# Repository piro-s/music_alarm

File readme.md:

# Music alarm:  
Playing music (sound signals) when the signal line breaks.  

### Schemes:  
###### Music_alarm_v0.1:  
[pdf](docs/music_alarm_v0.1.pdf)  

### Images:  
###### Music_alarm_v0.1:  
top:  
  
bottom:  

###### gerber:  
Archive for production:  
[Music_alarm_v0.1](https://github.com/piro-s/music_alarm/raw/main/gerber/music_alarm_v0.1.zip)

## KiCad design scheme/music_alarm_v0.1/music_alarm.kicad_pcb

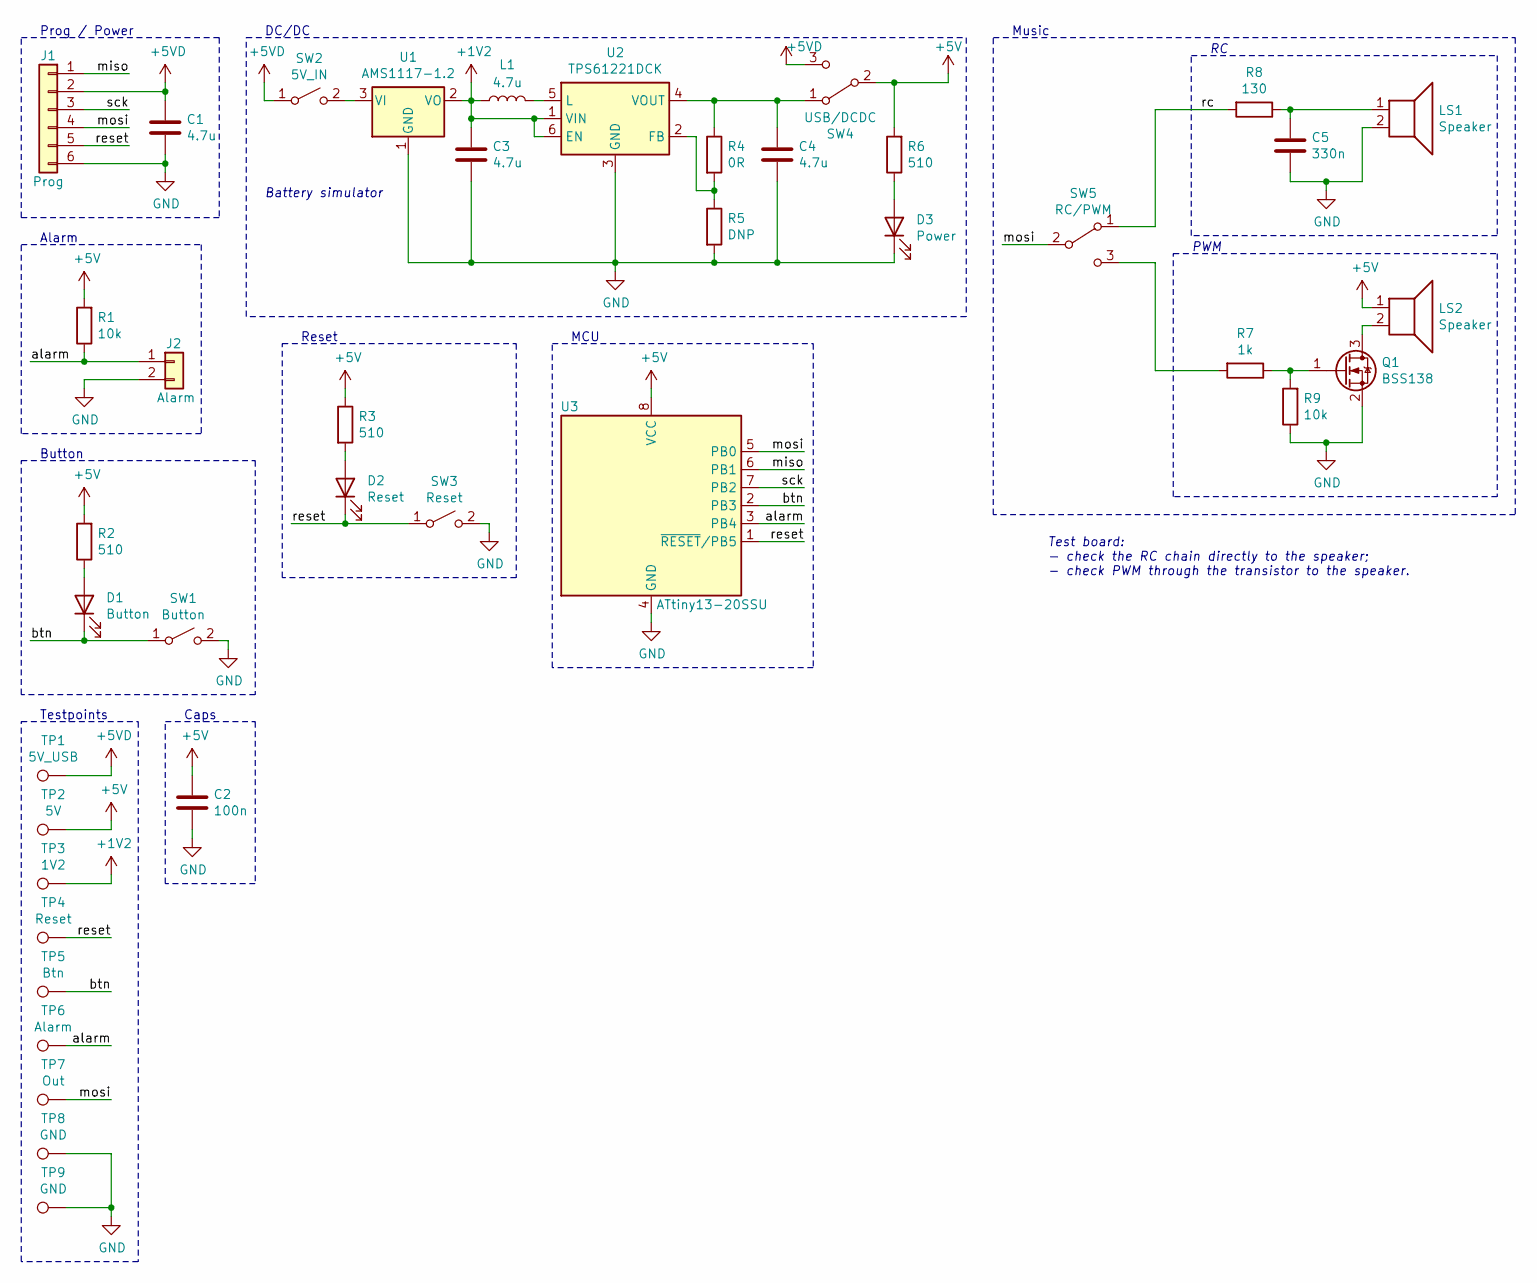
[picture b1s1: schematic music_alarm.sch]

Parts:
C1, C3, C4: 4.7u; C_1206_3216Metric_Pad1.33x1.80mm_HandSolder
C2: 100n; C_0603_1608Metric_Pad1.08x0.95mm_HandSolder
C5: 330n; C_0603_1608Metric_Pad1.08x0.95mm_HandSolder
D1: Button; LED_0603_1608Metric_Pad1.05x0.95mm_HandSolder
D2: Reset; LED_0603_1608Metric_Pad1.05x0.95mm_HandSolder
D3: Power; LED_0603_1608Metric_Pad1.05x0.95mm_HandSolder
J1: Prog; IDC-Header_2x06_P2.54mm_Vertical
J2: Alarm; PinSocket_1x02_P1.27mm_Vertical
L1: 4.7u; L_0805_2012Metric_Pad1.05x1.20mm_HandSolder
LS1, LS2: Speaker; PinSocket_1x02_P1.27mm_Vertical
Q1: BSS138; SOT-23
R1, R9: 10k; R_0603_1608Metric_Pad0.98x0.95mm_HandSolder
R2, R3, R6: 510; R_0603_1608Metric_Pad0.98x0.95mm_HandSolder
R4: 0R; R_0603_1608Metric_Pad0.98x0.95mm_HandSolder
R5: DNP; R_0603_1608Metric_Pad0.98x0.95mm_HandSolder
R7: 1k; R_0603_1608Metric_Pad0.98x0.95mm_HandSolder
R8: 130; R_0603_1608Metric_Pad0.98x0.95mm_HandSolder
SW1: Button; SW_Push_1P1T_NO_6x6mm_H9.5mm
SW2: 5V_IN; PinHeader_1x02_P2.54mm_Vertical
SW3: Reset; SW_Push_1P1T_NO_6x6mm_H9.5mm
SW4: USB/DCDC; PinSocket_1x03_P2.54mm_Vertical
SW5: RC/PWM; PinSocket_1x03_P2.54mm_Vertical
TP1: 5V_USB; TestPoint_THTPad_D1.0mm_Drill0.5mm
TP2: 5V; TestPoint_THTPad_D1.0mm_Drill0.5mm
TP3: 1V2; TestPoint_THTPad_D1.0mm_Drill0.5mm
TP4: Reset; TestPoint_THTPad_D1.0mm_Drill0.5mm
TP5: Btn; TestPoint_THTPad_D1.0mm_Drill0.5mm
TP6: Alarm; TestPoint_THTPad_D1.0mm_Drill0.5mm
TP7: Out; TestPoint_THTPad_D1.0mm_Drill0.5mm
TP8, TP9: GND; TestPoint_THTPad_D1.0mm_Drill0.5mm
U1: AMS1117-1.2; SOT-223-3_TabPin2
U2: TPS61221DCK; Texas_R-PDSO-G6
U3: ATtiny13-20SSU; SOIC-8_3.9x4.9mm_P1.27mm

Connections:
+1V2: C3.1, L1.1, TP3.1, U1.2 (VO), U2.1 (VIN), U2.6 (EN)
+5V: C2.1, LS2.1, R1.2, R2.2, R3.1, R6.2, SW4.2 (B), TP2.1, U3.8 (VCC)
+5VD: C1.1, J1.2, SW2.1 (A), SW4.3 (C), TP1.1
/alarm: J2.1, R1.1, TP6.1, U3.3 (PB4)
/btn: D1.1 (K), SW1.1 (A), TP5.1, U3.2 (PB3)
/miso: J1.1, U3.6 (PB1)
/mosi: J1.4, SW5.2 (B), TP7.1, U3.5 (PB0)
/rc: R8.2, SW5.1 (A)
/reset: D2.1 (K), J1.5, SW3.1 (A), TP4.1, U3.1 (~RESET~/PB5)
/sck: J1.3, U3.7 (PB2)
GND: C1.2, C2.2, C3.2, C4.2, C5.2, D3.1 (K), J1.6, J2.2, LS1.2, Q1.2 (S), R5.2, R9.1, SW1.2 (B), SW3.2 (B), TP8.1, TP9.1, U1.1 (GND), U2.3 (GND), U3.4 (GND)
unnamed: C4.1, R4.1, SW4.1 (A), U2.4 (VOUT)
unnamed: C5.1, LS1.1, R8.1
unnamed: D1.2 (A), R2.1
unnamed: D2.2 (A), R3.2
unnamed: D3.2 (A), R6.1
unnamed: L1.2, U2.5 (L)
unnamed: LS2.2, Q1.3 (D)
unnamed: Q1.1 (G), R7.1, R9.2
unnamed: R4.2, R5.1, U2.2 (FB)
unnamed: R7.2, SW5.3 (C)
unnamed: SW2.2 (B), U1.3 (VI)

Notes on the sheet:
Test board: - check the RC chain directly to the speaker; - check PWM through the transistor to the speaker.
Prog / Power
Reset
MCU
PWM
Music
Button
Alarm
DC/DC
Battery simulator
Testpoints
Caps

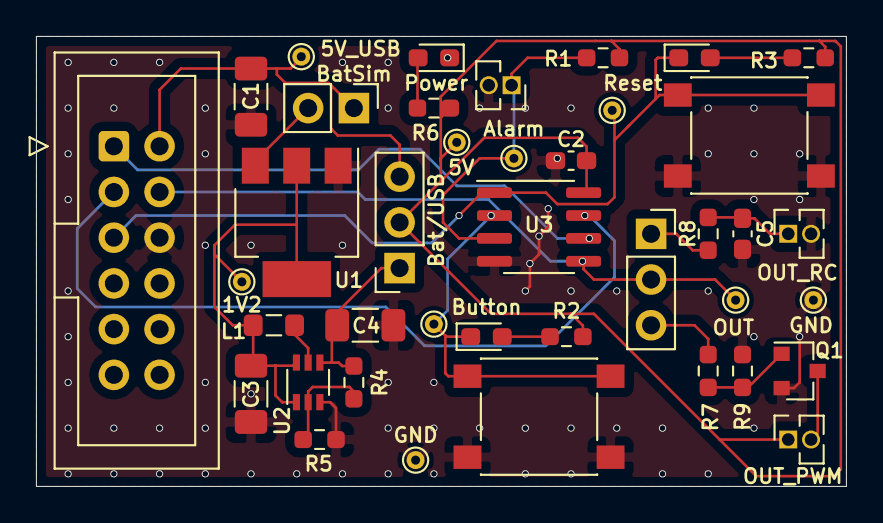
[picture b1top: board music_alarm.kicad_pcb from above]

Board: 2 copper layers, 45.0 x 25.0 mm, 40 parts (0 on the bottom side), 22 nets.

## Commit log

2024-04-30 Initial
2024-04-30 small: Gerber link
    Fix gerber link.
2024-05-02 small: QR code
    Change QR code from github to site.
